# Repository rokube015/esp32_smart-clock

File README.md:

# ESP32-smart-clock

This repository provides firmware and PCB design for a clock with environmental monitoring project using the ESP-IDF framework.

## Features
- CO2, temperature, humidity and atmosphere pressure monitoring.
- Custom PCB design for the project.

## Prerequisites

### Software Requirements
- ESP-IDF version 6.1 (ESP32-S3 target)
- Python 3.x
## Setup
1. **Install ESP-IDF**: Follow the [ESP-IDF Getting Started Guide](https://docs.espressif.com/projects/esp-idf/en/latest/esp32/get-started/index.html).
2. **Clone the Repository**:
   ```bash
   git clone https://github.com/rokube015/esp32_smart-clock.git
   ```
3. **Configure Wi-Fi on first boot**: Flash and start the device, then use Espressif's SoftAP Provisioning app to connect to the `SMART_CLOCK_<MAC>` setup network. Enter the proof of possession (PoP) printed in the serial log, then select your Wi-Fi network and enter its password in the app. The credentials are stored by ESP-IDF in NVS and reused on later boots. The setup access point is open, but provisioning messages are encrypted using the one-time PoP.

   If connection to the saved network fails repeatedly, the device starts SoftAP provisioning again so you can configure a new network.
## License
This project is licensed under the [Apache License 2.0](./LICENSE).

### Third-Party Licenses

This project utilizes the following third-party libraries:

- **[ESP-IDF](https://github.com/espressif/esp-idf)** - Licensed under the Apache License 2.0
- **[FreeRTOS](https://github.com/FreeRTOS/FreeRTOS)** - Licensed under the MIT License
- **[LovyanGFX](https://github.com/lovyan03/LovyanGFX)** - Licensed under the MIT License

Each library is subject to its own license terms. Please refer to the respective repositories for more information.
## Contributing
Contributions are welcome!
Please use the Issues tab to report bugs or suggest features, and feel free to submit pull requests.

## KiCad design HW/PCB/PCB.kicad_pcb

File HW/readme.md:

# Hardware Information

This folder contains PCB design files for the ESP32 Smart Clock.

## PCB Folder
The `PCB/` folder contains KiCad project files for the ESP32 Smart Clock.

## Files Description
- **PCB_layout.pdf**: PCB design layout.
- **schematic.pdf**: Circuit schematic diagram.
- **Bom.csv**: List of components required to build the SmartClock.

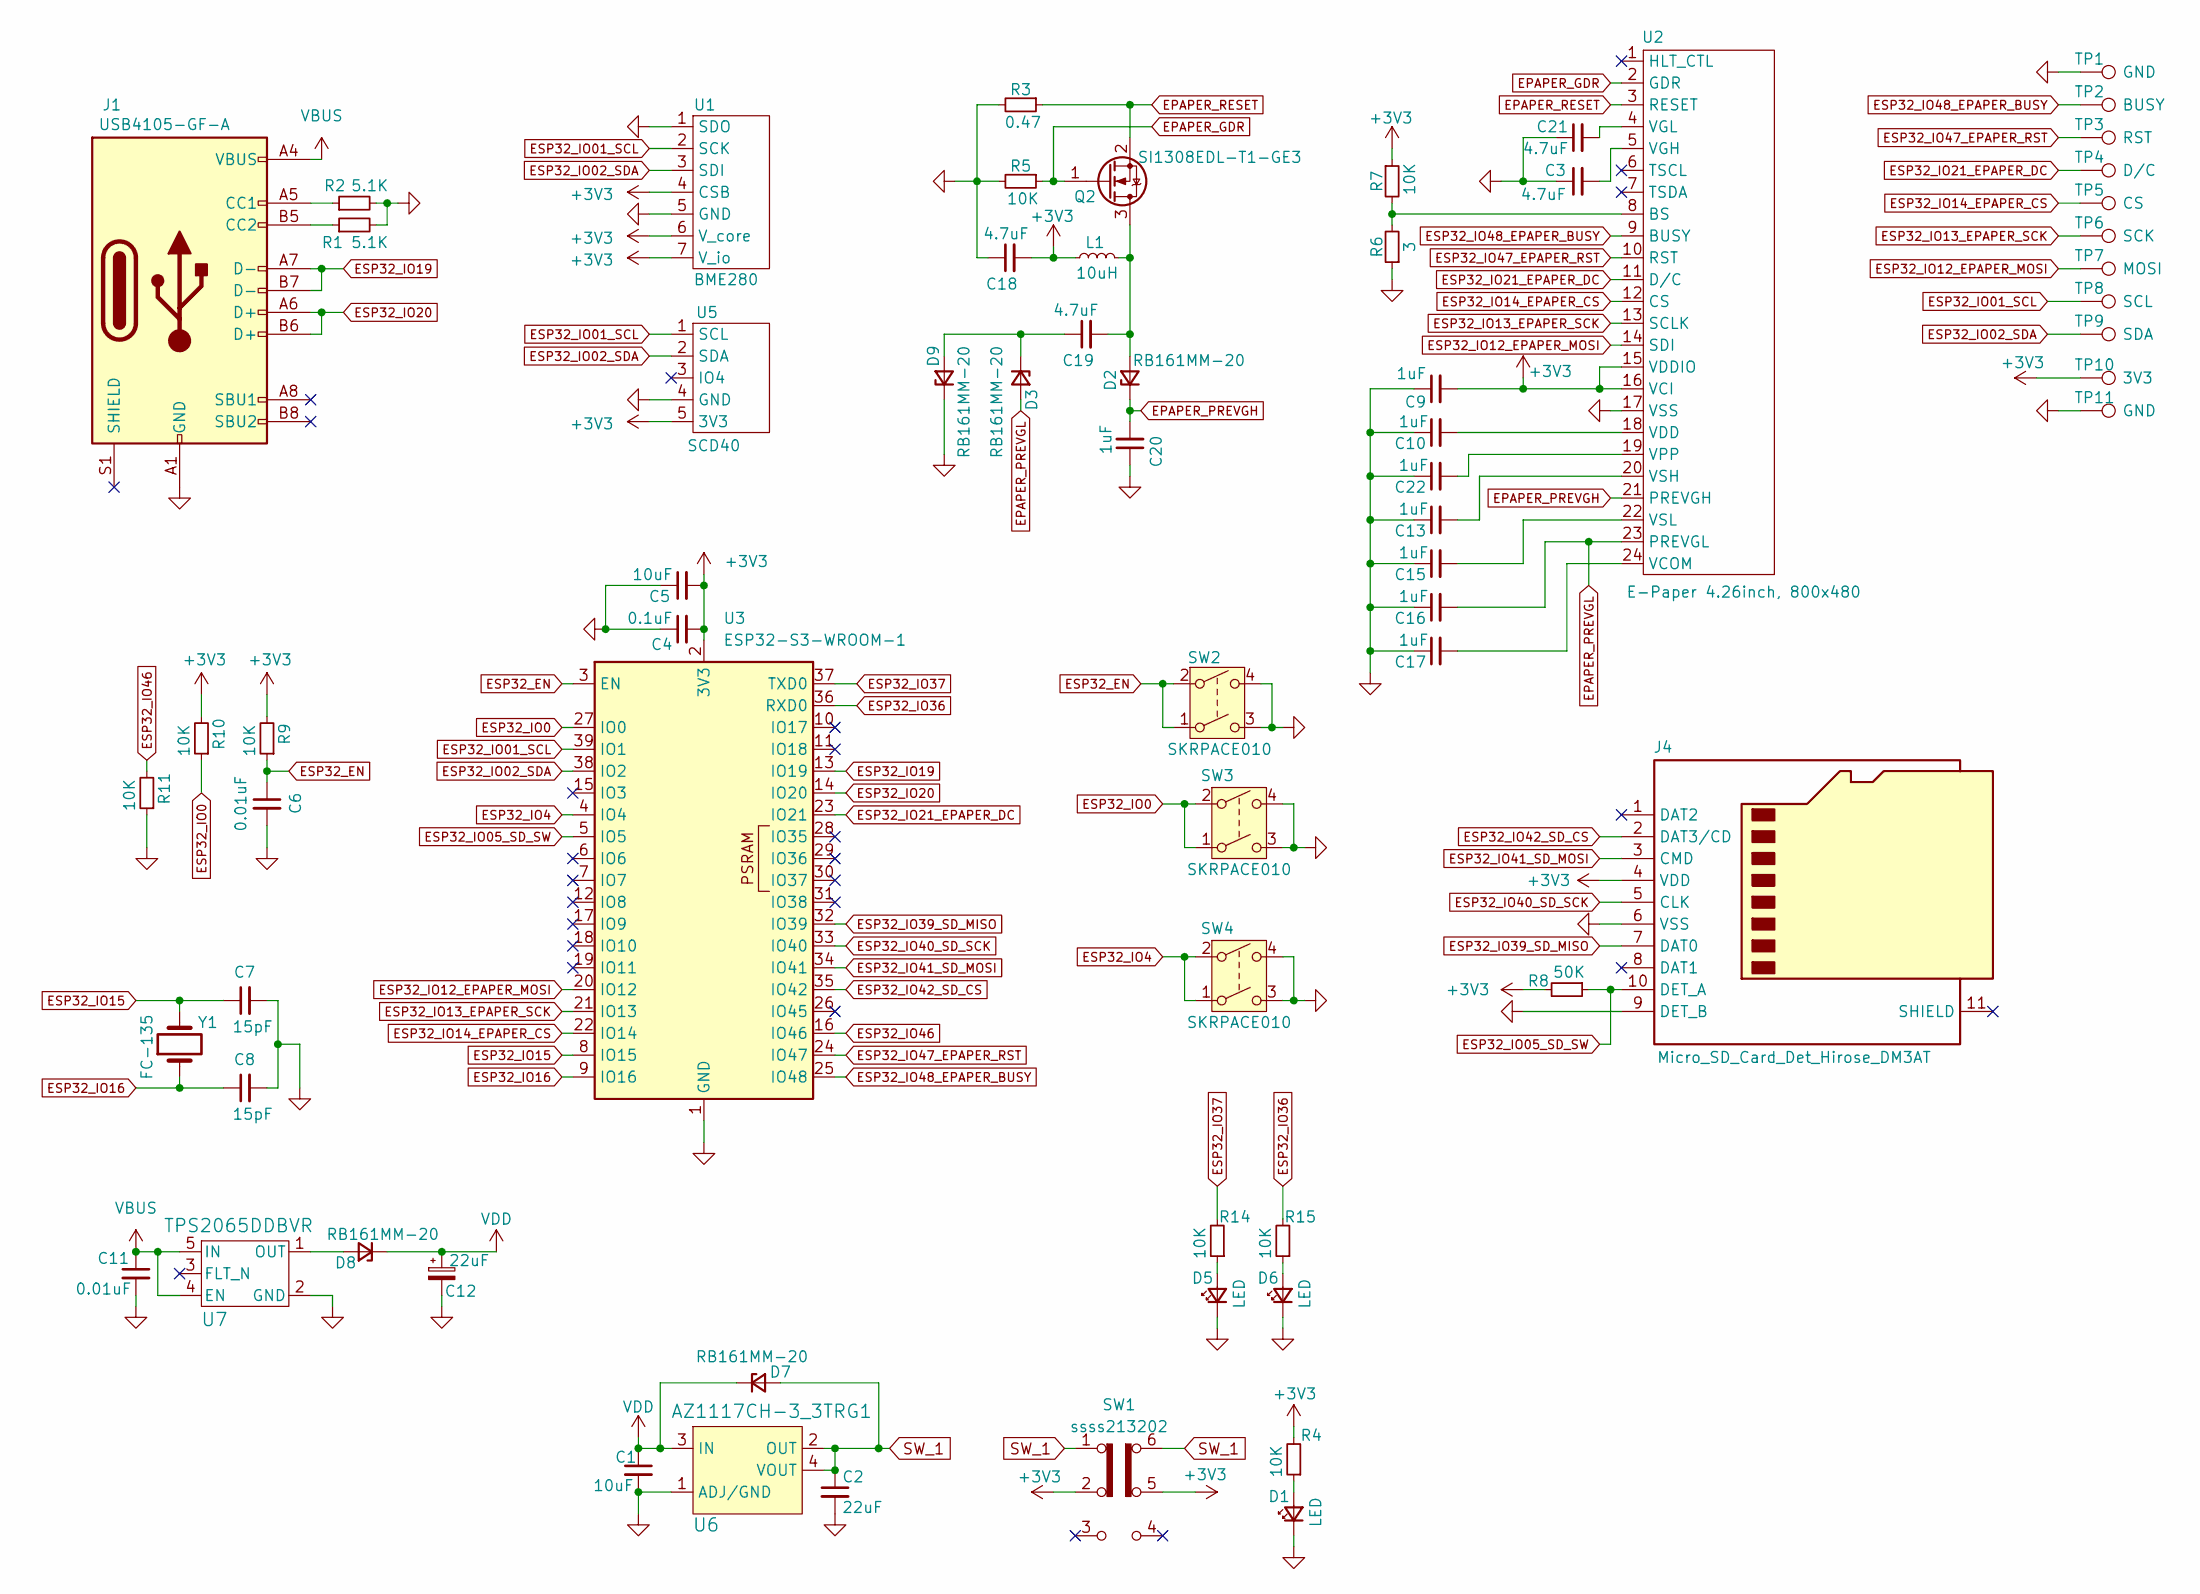
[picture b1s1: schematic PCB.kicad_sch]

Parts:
C1, C5: 10uF; C_0603_1608Metric_Pad1.08x0.95mm_HandSolder
C2: 22uF; C_0603_1608Metric_Pad1.08x0.95mm_HandSolder
C3, C18, C19, C21: 4.7uF; C_0603_1608Metric_Pad1.08x0.95mm_HandSolder
C4: 0.1uF; C_0805_2012Metric_Pad1.18x1.45mm_HandSolder
C6, C11: 0.01uF; C_0603_1608Metric_Pad1.08x0.95mm_HandSolder
C7, C8: 15pF; C_0603_1608Metric_Pad1.08x0.95mm_HandSolder
C9, C10, C13, C15, C16, C17, C20, C22: 1uF; C_0805_2012Metric_Pad1.18x1.45mm_HandSolder
C12: 22uF; TAJB_AVX
D1, D5, D6: LED; LED_0603_1608Metric_Pad1.05x0.95mm_HandSolder
D2, D3, D7, D8, D9: RB161MM-20; D_SOD-123
J1: USB4105-GF-A; USB-C31-S-VT-CS4-BK-PP-TR
J4: Micro_SD_Card_Det_Hirose_DM3AT; microSD_HC_Hirose_DM3AT-SF-PEJM5
L1: 10uH; AMP10420ED
Q2: SI1308EDL-T1-GE3; SOT-323_SC-70_Handsoldering
R1, R2: 5.1K; R_1206_3216Metric_Pad1.30x1.75mm_HandSolder
R3: 0.47; R_1206_3216Metric_Pad1.30x1.75mm_HandSolder
R4, R5, R7, R9, R10, R11, R14, R15: 10K; R_1206_3216Metric_Pad1.30x1.75mm_HandSolder
R6: 3; R_1206_3216Metric_Pad1.30x1.75mm_HandSolder
R8: 50K; R_1206_3216Metric_Pad1.30x1.75mm_HandSolder
SW1: ssss213202; SSSS213202
SW2, SW3, SW4: SKRPACE010
TP1, TP11: GND; TestPoint_THTPad_1.0x1.0mm_Drill0.5mm
TP2: BUSY; TestPoint_THTPad_D1.0mm_Drill0.5mm
TP3: RST; TestPoint_THTPad_D1.0mm_Drill0.5mm
TP4: D/C; TestPoint_THTPad_D1.0mm_Drill0.5mm
TP5: CS; TestPoint_THTPad_D1.0mm_Drill0.5mm
TP6: SCK; TestPoint_THTPad_D1.0mm_Drill0.5mm
TP7: MOSI; TestPoint_THTPad_D1.0mm_Drill0.5mm
TP8: SCL; TestPoint_THTPad_D1.0mm_Drill0.5mm
TP9: SDA; TestPoint_THTPad_D1.0mm_Drill0.5mm
TP10: 3V3; TestPoint_THTPad_D1.0mm_Drill0.5mm
U1: BME280; BME280_SwitchScience
U2: E-Paper 4.26inch, 800x480; CONN_XF2M-2415-1A_OMR
U3: ESP32-S3-WROOM-1
U5: SCD40; SCD40_Conta
U6: AZ1117CH-3_3TRG1; SOT-223; MPN AZ1117CH-3.3TRG1; Digi-Key_PN AZ1117CH-3.3TRG1DICT-ND
U7: TPS2065DDBVR; SOT-23-5
Y1: FC-135

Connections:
+3V3: C4.2, C5.2, C9.2, C18.2, J4.4 (VDD), L1.1, R4.2, R7.1, R8.2, R9.2, R10.2, SW1.2 (B), SW1.5 (B), TP10.1, U1.4 (CSB), U1.6 (V_core), U1.7 (V_io), U2.15 (VDDIO), U2.16 (VCI), U3.2 (3V3), U5.5 (3V3)
EPAPER_GDR: Q2.1 (G), R5.1, U2.2 (GDR)
EPAPER_PREVGH: C20.2, D2.1 (K), U2.21 (PREVGH)
EPAPER_PREVGL: C16.2, D3.2 (A), U2.23 (PREVGL)
EPAPER_RESET: Q2.2 (S), R3.1, U2.3 (RESET)
ESP32_EN: C6.1, R9.1, SW2.1, SW2.2, U3.3 (EN)
ESP32_IO0: R10.1, SW3.1, SW3.2, U3.27 (IO0)
ESP32_IO01_SCL: TP8.1, U1.2 (SCK), U3.39 (IO1), U5.1 (SCL)
ESP32_IO02_SDA: TP9.1, U1.3 (SDI), U3.38 (IO2), U5.2 (SDA)
ESP32_IO4: SW4.1, SW4.2, U3.4 (IO4)
ESP32_IO05_SD_SW: J4.10 (DET_A), R8.1, U3.5 (IO5)
ESP32_IO12_EPAPER_MOSI: TP7.1, U2.14 (SDI), U3.20 (IO12)
ESP32_IO13_EPAPER_SCK: TP6.1, U2.13 (SCLK), U3.21 (IO13)
ESP32_IO14_EPAPER_CS: TP5.1, U2.12 (CS), U3.22 (IO14)
ESP32_IO15: C7.1, U3.8 (IO15), Y1.2
ESP32_IO16: C8.1, U3.9 (IO16), Y1.1
ESP32_IO19: J1.A7 (D-), J1.B7 (D-), U3.13 (IO19)
ESP32_IO20: J1.A6 (D+), J1.B6 (D+), U3.14 (IO20)
ESP32_IO21_EPAPER_DC: TP4.1, U2.11 (D/C), U3.23 (IO21)
ESP32_IO36: R15.2, U3.36 (RXD0)
ESP32_IO37: R14.2, U3.37 (TXD0)
ESP32_IO39_SD_MISO: J4.7 (DAT0), U3.32 (IO39)
ESP32_IO40_SD_SCK: J4.5 (CLK), U3.33 (IO40)
ESP32_IO41_SD_MOSI: J4.3 (CMD), U3.34 (IO41)
ESP32_IO42_SD_CS: J4.2 (DAT3/CD), U3.35 (IO42)
ESP32_IO46: R11.2, U3.16 (IO46)
ESP32_IO47_EPAPER_RST: TP3.1, U2.10 (RST), U3.24 (IO47)
ESP32_IO48_EPAPER_BUSY: TP2.1, U2.9 (BUSY), U3.25 (IO48)
GND: C1.2, C2.2, C3.1, C4.1, C5.1, C6.2, C7.2, C8.2, C9.1, C10.1, C11.2, C12.2, C13.1, C15.1, C16.1, C17.1, C18.1, C20.1, C21.1, C22.1, D1.1 (K), D5.1 (K), D6.1 (K), D9.1 (K), J1.A1 (GND), J1.A12 (GND), J1.B1 (GND), J1.B12 (GND), J4.6 (VSS), J4.9 (DET_B), R1.2, R2.2, R3.2, R5.2, R6.1, R11.1, SW2.3, SW2.4, SW3.3, SW3.4, SW4.3, SW4.4, TP1.1, TP11.1, U1.1 (SDO), U1.5 (GND), U2.17 (VSS), U3.1 (GND), U3.40 (GND), U3.41 (GND), U5.4 (GND), U6.1 (ADJ/GND), U7.2 (GND)
unnamed: D1.2 (A), R4.1
unnamed: C19.2, D2.2 (A), L1.2, Q2.3 (D)
unnamed: C19.1, D3.1 (K), D9.2 (A)
unnamed: D5.2 (A), R14.1
unnamed: D6.2 (A), R15.1
unnamed: D8.2 (A), U7.1 (OUT)
unnamed: J1.A5 (CC1), R2.1
unnamed: J1.B5 (CC2), R1.1
unnamed: R6.2, R7.2, U2.8 (BS)
unnamed: C17.2, U2.24 (VCOM)
unnamed: C10.2, U2.18 (VDD)
unnamed: C3.2, U2.5 (VGH)
unnamed: C21.2, U2.4 (VGL)
unnamed: C22.2, U2.19 (VPP)
unnamed: C13.2, U2.20 (VSH)
unnamed: C15.2, U2.22 (VSL)
SW_1: C2.1, D7.2 (A), SW1.1 (A), SW1.6 (C), U6.2 (OUT), U6.4 (VOUT)
VBUS: C11.1, J1.A4 (VBUS), J1.A9 (VBUS), J1.B4 (VBUS), J1.B9 (VBUS), U7.4 (EN), U7.5 (IN)
VDD: C1.1, C12.1, D7.1 (K), D8.1 (K), U6.3 (IN)

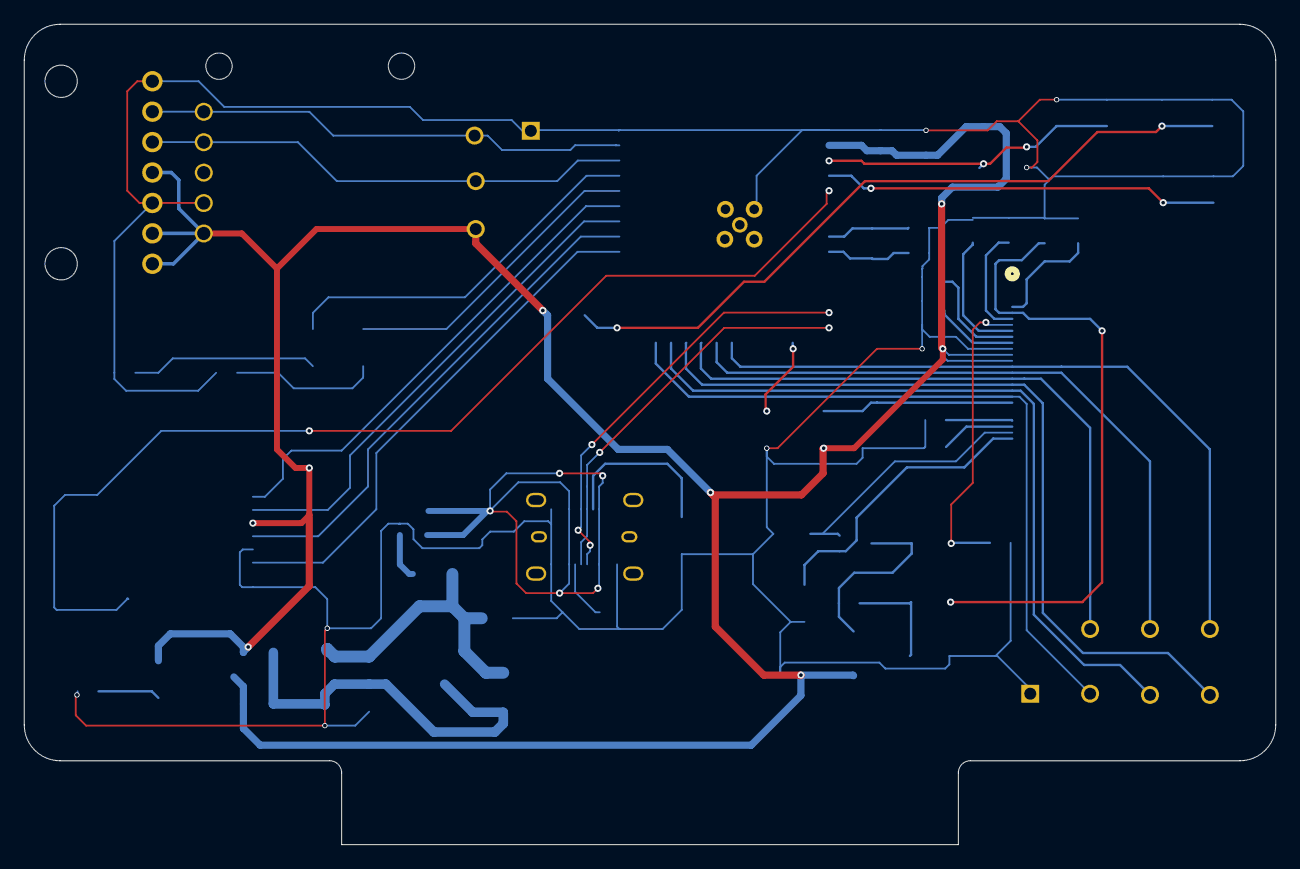
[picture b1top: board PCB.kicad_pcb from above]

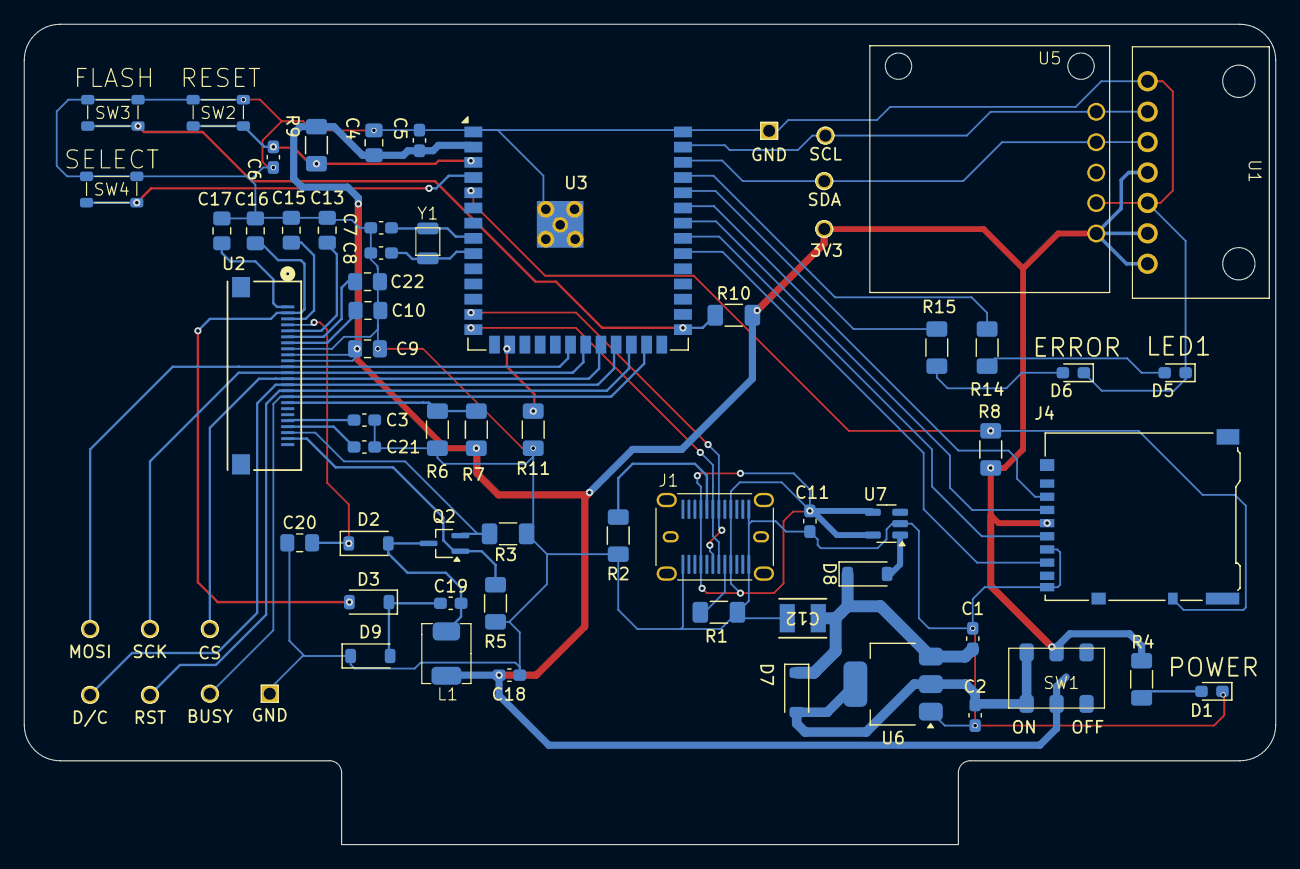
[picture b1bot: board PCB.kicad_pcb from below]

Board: 2 copper layers, 104.5 x 68.5 mm, 68 parts (68 on the bottom side), 48 nets.

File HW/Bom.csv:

Reference,Value,Datasheet,Footprint,Qty,DNP
"C1,C5",10uF,~,Capacitor_SMD:C_0603_1608Metric_Pad1.08x0.95mm_HandSolder,2,
"C2,C12",22uF,~,Capacitor_SMD:C_0603_1608Metric_Pad1.08x0.95mm_HandSolder,2,
"C3,C13,C15,C16,C18,C19,C20,C21",4.7uF,~,Capacitor_SMD:C_0603_1608Metric_Pad1.08x0.95mm_HandSolder,8,
C4,0.1uF,~,Capacitor_SMD:C_0805_2012Metric_Pad1.18x1.45mm_HandSolder,1,
"C6,C11",0.01uF,~,Capacitor_SMD:C_0603_1608Metric_Pad1.08x0.95mm_HandSolder,2,
"C7,C8",15pF,~,Capacitor_SMD:C_0603_1608Metric_Pad1.08x0.95mm_HandSolder,2,
"C9,C10,C17,C22",1uF,~,Capacitor_SMD:C_0603_1608Metric_Pad1.08x0.95mm_HandSolder,4,
"D1,D5,D6",LED,~,LED_SMD:LED_0603_1608Metric_Pad1.05x0.95mm_HandSolder,3,
"D2,D3,D7,D8,D9",RB161MM-20,~,Diode_SMD:D_SOD-123,5,
J1,USB4105-GF-A,https://www.usb.org/sites/default/files/documents/usb_type-c.zip,mylib:USB-C31-S-VT-CS4-BK-PP-TR,1,
J4,Micro_SD_Card_Det_Hirose_DM3AT,https://www.hirose.com/product/en/download_file/key_name/DM3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,Connector_Card:microSD_HC_Hirose_DM3AT-SF-PEJM5,1,
L1,10uH,~,mylib:AMP10420ED,1,
Q2,SI1308EDL-T1-GE3,https://www.onsemi.com/pub/Collateral/BSS138-D.PDF,Package_TO_SOT_SMD:SOT-323_SC-70_Handsoldering,1,
"R1,R2",5.1K,~,Resistor_SMD:R_1206_3216Metric_Pad1.30x1.75mm_HandSolder,2,
R3,0.47,~,Resistor_SMD:R_1206_3216Metric_Pad1.30x1.75mm_HandSolder,1,
"R4,R5,R7,R9,R10,R11,R14,R15",10K,~,Resistor_SMD:R_1206_3216Metric_Pad1.30x1.75mm_HandSolder,8,
R6,3,~,Resistor_SMD:R_1206_3216Metric_Pad1.30x1.75mm_HandSolder,1,
R8,50K,~,Resistor_SMD:R_1206_3216Metric_Pad1.30x1.75mm_HandSolder,1,
SW1,ssss213202,~,mylib:SSSS213202,1,
"SW2,SW3,SW4",SKRPACE010,~,mylib:SKRPACE010,3,
"TP1,TP11",GND,~,TestPoint:TestPoint_THTPad_1.0x1.0mm_Drill0.5mm,2,
TP2,BUSY,~,TestPoint:TestPoint_THTPad_D1.0mm_Drill0.5mm,1,
TP3,RST,~,TestPoint:TestPoint_THTPad_D1.0mm_Drill0.5mm,1,
TP4,D/C,~,TestPoint:TestPoint_THTPad_D1.0mm_Drill0.5mm,1,
TP5,CS,~,TestPoint:TestPoint_THTPad_D1.0mm_Drill0.5mm,1,
TP6,SCK,~,TestPoint:TestPoint_THTPad_D1.0mm_Drill0.5mm,1,
TP7,MOSI,~,TestPoint:TestPoint_THTPad_D1.0mm_Drill0.5mm,1,
TP8,SCL,~,TestPoint:TestPoint_THTPad_D1.0mm_Drill0.5mm,1,
TP9,SDA,~,TestPoint:TestPoint_THTPad_D1.0mm_Drill0.5mm,1,
TP10,3V3,~,TestPoint:TestPoint_THTPad_D1.0mm_Drill0.5mm,1,
U1,BME280,,mylib:BME280_SwitchScience,1,
U2,"E-Paper 4.26inch, 800x480",https://www.waveshare.com/4.26inch-e-paper.htm,XF2M-2415-1A:CONN_XF2M-2415-1A_OMR,1,
U4,ESP32-S3-WROOM-1,https://www.espressif.com/sites/default/files/documentation/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,mylib:ESP32-S3-WROOM-1,1,
U5,SCD40,,mylib:SCD40_Conta,1,
U6,AZ1117CH-3_3TRG1,,Package_TO_SOT_SMD:SOT-223,1,
U7,TPS2065DDBVR,TPS2065DDBVR,Package_TO_SOT_SMD:SOT-23-5,1,
Y1,FC-135,~,mylib:FC-135,1,
-,Card stand,https://www.amazon.co.jp/gp/product/B0BGGFBQXZ/ref=ppx_yo_dt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,-,1,
-,Thermal Conductive Silicone Pads,https://www.amazon.co.jp/gp/product/B07RW81T8W/ref=ppx_yo_dt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,-,1,

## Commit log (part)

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2024-07-21 add esp32 file
2024-07-21 add scd40.c and scd40.h
2024-08-31 Add read CO2, humidity adn temperature from scd40
2024-08-31 Add sd card interface
2024-08-31 Modify gitignore
2024-08-31 Add output Scd40 read data to SD card
2024-08-31 Remove esp32/build directory
2024-08-31 Remove esp32/main/build directory
2024-08-31 Updata .gitignore file.
2024-09-01 Modify gitignore file
2024-09-08 Add function for set temperature offset on scd40.
2024-09-15 add set temperature offset function
2024-09-21 modify scd40.c for refactoring
2024-09-21 modify main.c for refactoring
2024-09-21 add get time function form sntp server
2024-09-22 add wifi.c and wifi.h
2024-09-22 modify output log for sensor data
2024-09-22 fix main/main.c
2024-09-28 add retry stop periodic measurement command
2024-09-28 add bme.c and bme.h
2024-09-29 add bme280 sensor read function
2024-09-29 change sdcard filepath
2024-09-29 change output log file name.
2024-09-29 refactoring for main.c
2024-09-29 add HW file for PCB
2024-10-13 add kicad data
2024-11-09 Add PCB layout
2024-11-09 add schematic file
2024-11-30 modify PCB layout
2024-12-01 change project/esp32 file name to projecr/SW
2024-12-01 change CMakeLists.txt for build C++
2024-12-01 add i2c_base component
2024-12-01 add bme280 component
2024-12-01 add gpio components
2024-12-08 modify i2c interface for using new i2c esp-idf lib.
2024-12-08 modify i2c interface function
2024-12-14 add gaber data
2024-12-14 add PMIC
2024-12-15 modify PCB design pattern
2024-12-20 add guber date
2024-12-21 add scd40 component
2024-12-22 add wifi components for get time from sntp server.
2024-12-28 add sd card compornent
2024-12-28 add to sensor data write function
2024-12-28 change pressure output format from Pa to hPa.
2024-12-29 modify sdkconfig
2024-12-29 change target SoC to ESP32-S3 from ESP32
2024-12-29 change i2c port settings
2024-12-30 add i2c_port_mutex
2024-12-31 add smart_clock class
2024-12-31 modify smart_clock component.
2024-12-31 add scd40 co2_measurement task
2024-12-31 add measure bme280 sensor data task.
2025-01-01 modify scd40 task
2025-01-01 modify bm280 measure task
2025-01-01 add task notify function.
2025-01-02 add AQM0802A function for display co2.
2025-01-18 add display/e_paper component.
2025-01-18 change wait time for display update
2025-01-19 add submodule: LovyanGFX
2025-01-19 modified submodule locally.
2025-01-19 change smart_clock component.
2025-01-19 add e_paper component.
2025-01-19 display clock and co2 on e-paper
2025-01-19 change output format.
2025-02-02 add e-paper module
2025-02-02 add epaper components
2025-02-08 add update_display task
2025-02-09 refactor smart_clock class
2025-02-11 refctor scd40 components
2025-02-11 modify vTaskDelay time in main.cpp
2025-02-15 modify schematics
2025-02-16 Order HW/PCB/ESP32_SmartClock_GBR_ELECROW.zip to Elecrow (#243165)
2025-02-16 add readme
2025-02-16 add Bom fail
2025-02-16 add kicad symbol file.
2025-02-17 Create LICENSE
2025-02-22 add doxygen comment in i2c_base.h
2025-02-24 add error log
2025-03-07 change PCB design
2025-03-09 change PCD layout
2025-03-22 Create images
2025-03-22 change source file.
2025-03-22 change header file.
2025-03-22 change file name.
2025-03-23 add week number display
